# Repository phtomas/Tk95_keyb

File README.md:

Gerbers files to produce TK95 keyboard boards to substitute membranes. you can use original acetate and upper membrane to make contact for the keys, since at least key contact points are working. Or you can coat that points with some conduct ink or even stick some conduct material in that or use MX switches for a complete mechanical keyboard.

Based on Don Superfo schematics. original at: https://www.pcbway.com/project/shareproject/ZX_Spectrum_Keyboard_V2_14d9c665.html

Special thanks to Alexandre Simonka who has sponsered this project and Marlos Vasconcelos for moral support. Many thanks my friends.

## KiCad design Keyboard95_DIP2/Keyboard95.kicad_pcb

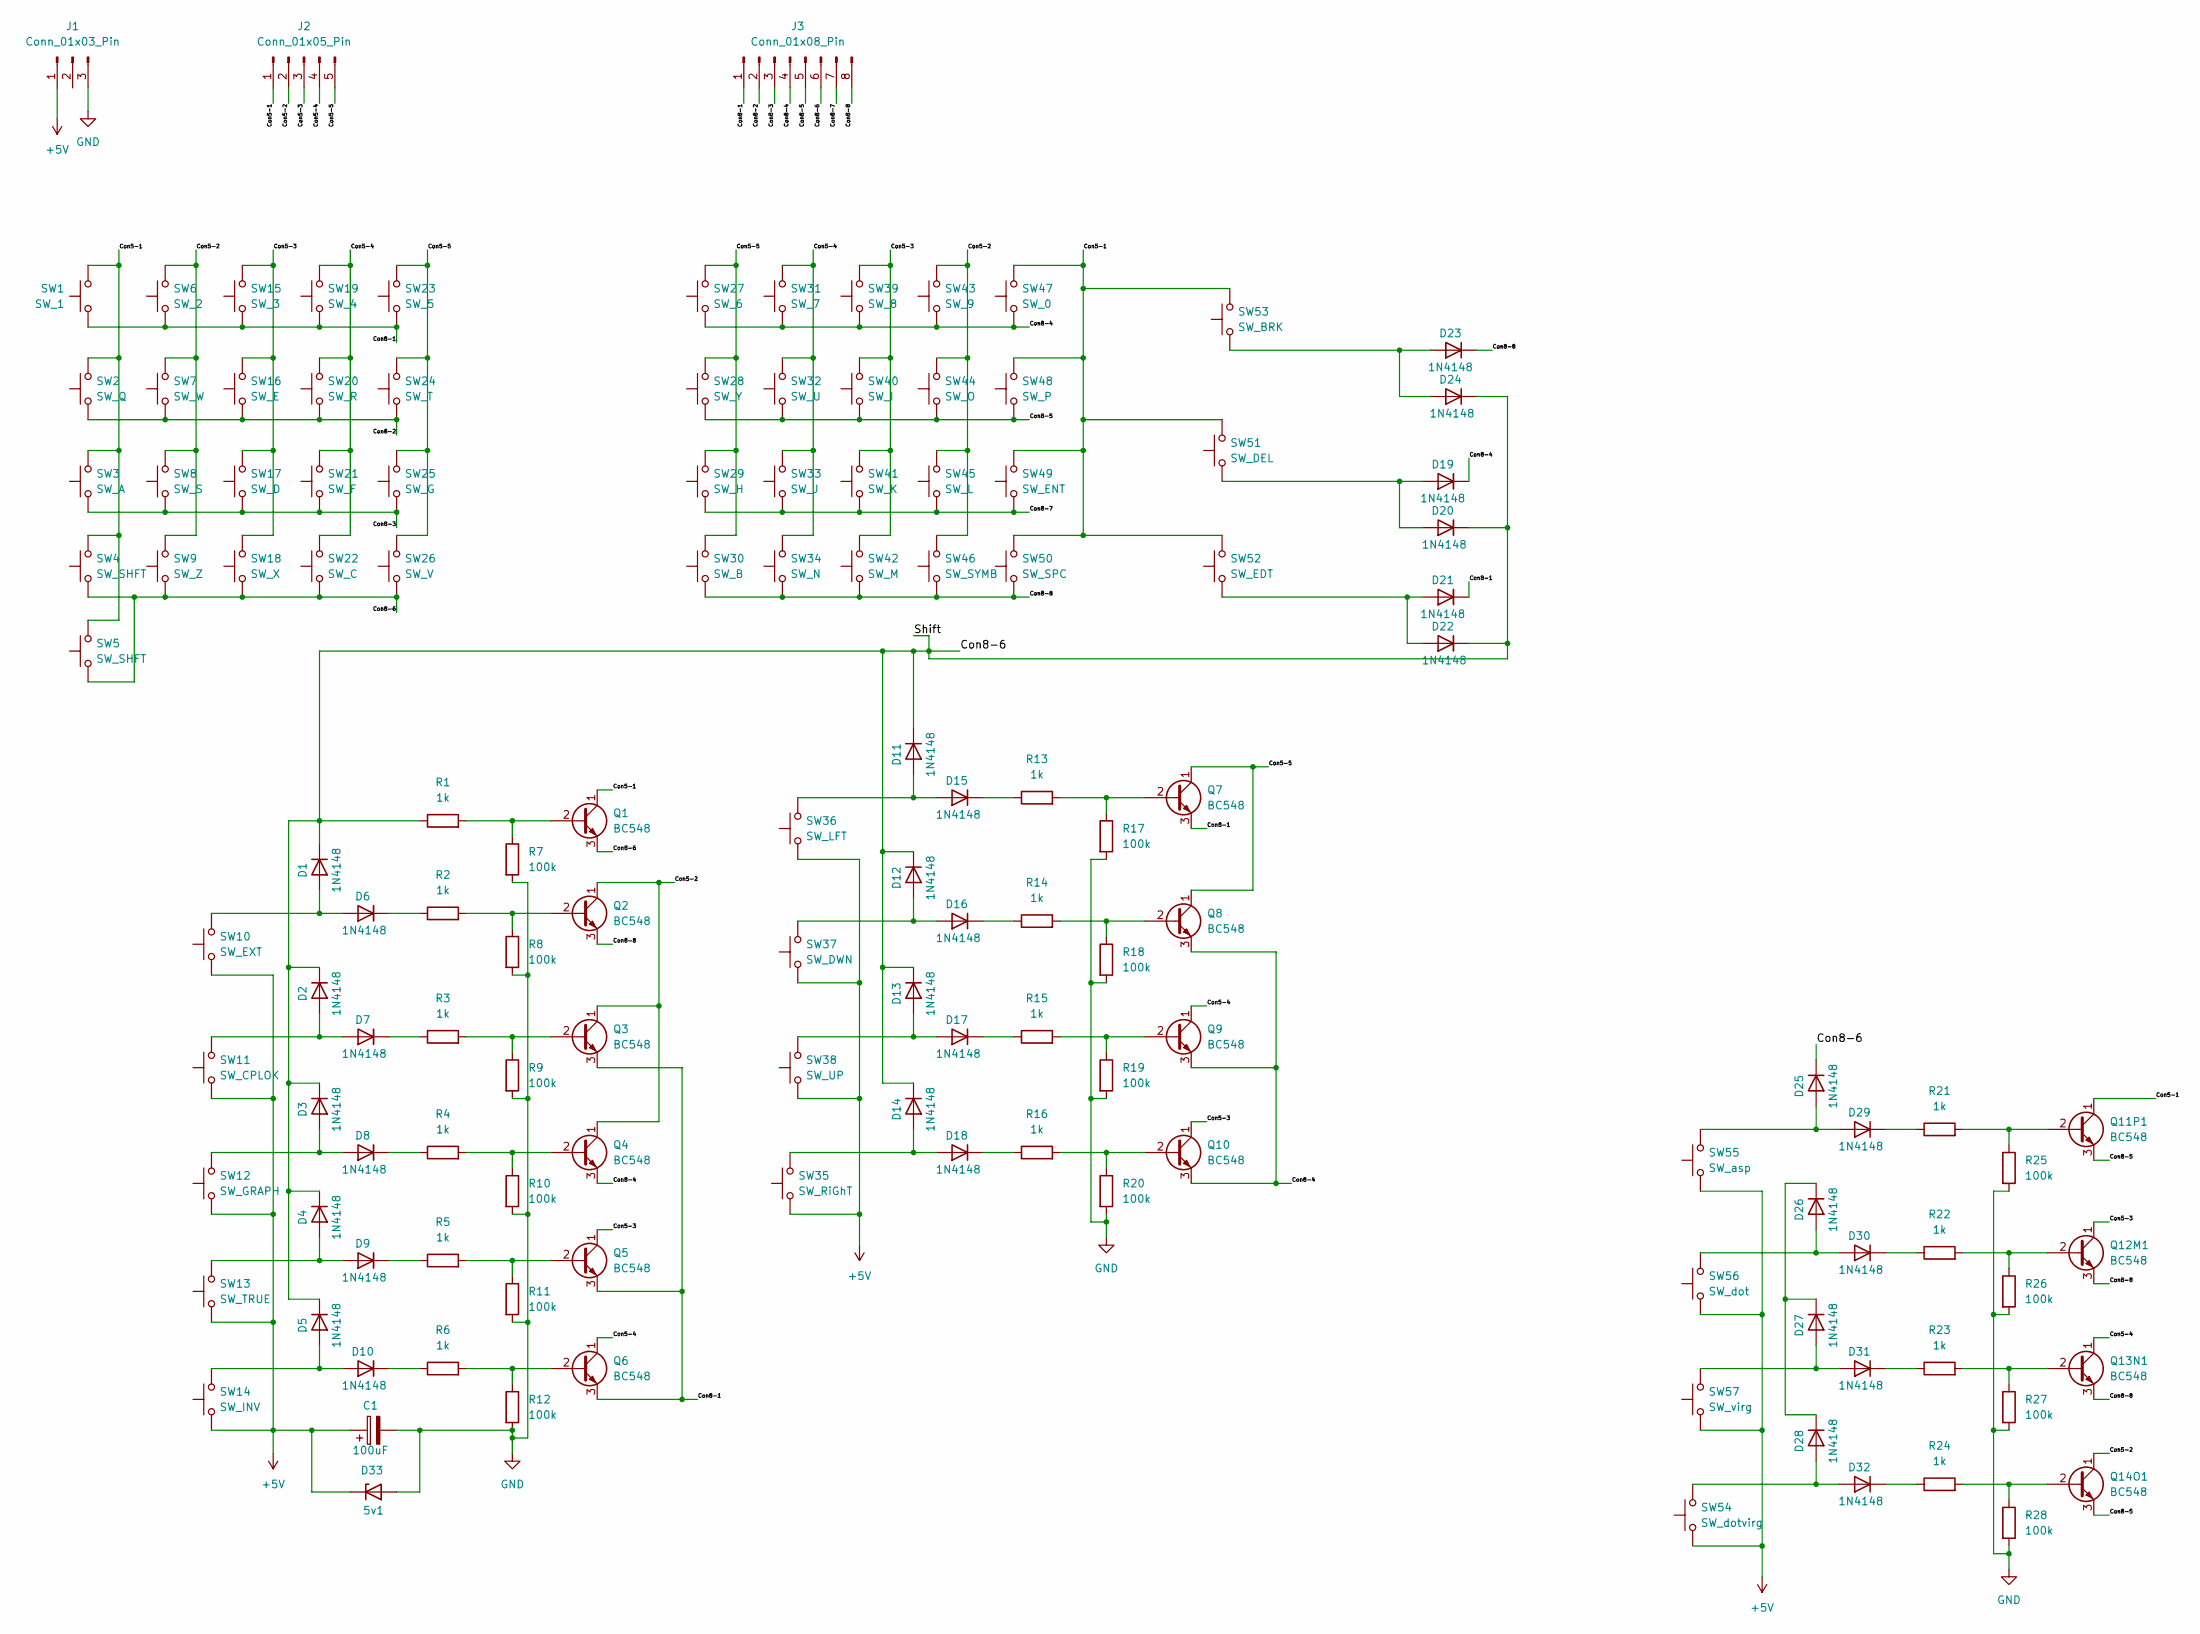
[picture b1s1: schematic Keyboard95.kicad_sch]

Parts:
C1: 100uF; CP_Radial_D5.0mm_P2.50mm
D1, D2, D3, D4, D5, D6, D7, D8, D9, D10, D11, D12, D13, D14, D15, D16, D17, D18, D19, D20, D21, D22, D23, D24, D25, D26, D27, D28, D29, D30, D31, D32: 1N4148; D_DO-35_SOD27_P7.62mm_Horizontal
D33: 5v1; D_A-405_P7.62mm_Horizontal
J1: Conn_01x03_Pin; PinHeader_1x03_P2.54mm_Vertical
J2: Conn_01x05_Pin; PinHeader_1x05_P2.54mm_Vertical
J3: Conn_01x08_Pin; PinHeader_1x08_P2.54mm_Vertical
Q1, Q2, Q3, Q4, Q5, Q6, Q7, Q8, Q9, Q10, Q11P1, Q12M1, Q13N1, Q14O1: BC548; TO-92_Inline
R1, R2, R3, R4, R5, R6, R13, R14, R15, R16, R21, R22, R23, R24: 1k; R_Box_L8.4mm_W2.5mm_P5.08mm
R7, R8, R9, R10, R11, R12, R17, R18, R19, R20, R25, R26, R27, R28: 100k; R_Box_L8.4mm_W2.5mm_P5.08mm
SW1: SW_1; SW_SMD_key
SW2: SW_Q; SW_SMD_key
SW3: SW_A; SW_SMD_key
SW4, SW5: SW_SHFT; SW_SMD_key
SW6: SW_2; SW_SMD_key
SW7: SW_W; SW_SMD_key
SW8: SW_S; SW_SMD_key
SW9: SW_Z; SW_SMD_key
SW10: SW_EXT; SW_SMD_key
SW11: SW_CPLOK; SW_SMD_key
SW12: SW_GRAPH; SW_SMD_key
SW13: SW_TRUE; SW_SMD_key
SW14: SW_INV; SW_SMD_key
SW15: SW_3; SW_SMD_key
SW16: SW_E; SW_SMD_key
SW17: SW_D; SW_SMD_key
SW18: SW_X; SW_SMD_key
SW19: SW_4; SW_SMD_key
SW20: SW_R; SW_SMD_key
SW21: SW_F; SW_SMD_key
SW22: SW_C; SW_SMD_key
SW23: SW_5; SW_SMD_key
SW24: SW_T; SW_SMD_key
SW25: SW_G; SW_SMD_key
SW26: SW_V; SW_SMD_key
SW27: SW_6; SW_SMD_key
SW28: SW_Y; SW_SMD_key
SW29: SW_H; SW_SMD_key
SW30: SW_B; SW_SMD_key
SW31: SW_7; SW_SMD_key
SW32: SW_U; SW_SMD_key
SW33: SW_J; SW_SMD_key
SW34: SW_N; SW_SMD_key
SW35: SW_RiGhT; SW_SMD_key
SW36: SW_LFT; SW_SMD_key
SW37: SW_DWN; SW_SMD_key
SW38: SW_UP; SW_SMD_key
SW39: SW_8; SW_SMD_key
SW40: SW_I; SW_SMD_key
SW41: SW_K; SW_SMD_key
SW42: SW_M; SW_SMD_key
SW43: SW_9; SW_SMD_key
SW44: SW_O; SW_SMD_key
SW45: SW_L; SW_SMD_key
SW46: SW_SYMB; SW_SMD_key
SW47: SW_0; SW_SMD_key
SW48: SW_P; SW_SMD_key
SW49: SW_ENT; SW_SMD_key
SW50: SW_SPC; SW_SMD_key
SW51: SW_DEL; SW_SMD_key
SW52: SW_EDT; SW_SMD_key
SW53: SW_BRK; SW_SMD_key
SW54: SW_dotvirg; SW_SMD_key
SW55: SW_asp; SW_SMD_key
SW56: SW_dot; SW_SMD_key
SW57: SW_virg; SW_SMD_key

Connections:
+5V: C1.1, D33.1 (K), J1.1, SW10.1, SW11.1, SW12.1, SW13.1, SW14.1, SW35.1, SW36.1, SW37.1, SW38.1, SW54.1, SW55.1, SW56.1, SW57.1
/Con5-1: J2.1, Q1.1 (C), Q11P1.1 (C), SW1.2, SW2.2, SW3.2, SW4.2, SW5.2, SW47.2, SW48.2, SW49.2, SW50.2, SW51.2, SW52.2, SW53.2
/Con5-2: J2.2, Q2.1 (C), Q3.1 (C), Q4.1 (C), Q14O1.1 (C), SW6.2, SW7.2, SW8.2, SW9.2, SW43.2, SW44.2, SW45.2, SW46.2
/Con5-3: J2.3, Q5.1 (C), Q10.1 (C), Q12M1.1 (C), SW15.2, SW16.2, SW17.2, SW18.2, SW39.2, SW40.2, SW41.2, SW42.2
/Con5-4: J2.4, Q6.1 (C), Q9.1 (C), Q13N1.1 (C), SW19.2, SW20.2, SW21.2, SW22.2, SW31.2, SW32.2, SW33.2, SW34.2
/Con5-5: J2.5, Q7.1 (C), Q8.1 (C), SW23.2, SW24.2, SW25.2, SW26.2, SW27.2, SW28.2, SW29.2, SW30.2
/Con8-1: D21.1 (K), J3.1, Q3.3 (E), Q5.3 (E), Q6.3 (E), Q7.3 (E), SW1.1, SW6.1, SW15.1, SW19.1, SW23.1
/Con8-2: J3.2, SW2.1, SW7.1, SW16.1, SW20.1, SW24.1
/Con8-3: J3.3, SW3.1, SW8.1, SW17.1, SW21.1, SW25.1
/Con8-4: D19.1 (K), J3.4, Q4.3 (E), Q8.3 (E), Q9.3 (E), Q10.3 (E), SW27.1, SW31.1, SW39.1, SW43.1, SW47.1
/Con8-5: J3.5, Q11P1.3 (E), Q14O1.3 (E), SW28.1, SW32.1, SW40.1, SW44.1, SW48.1
/Con8-6: D1.1 (K), D2.1 (K), D3.1 (K), D4.1 (K), D5.1 (K), D11.1 (K), D12.1 (K), D13.1 (K), D14.1 (K), D20.1 (K), D22.1 (K), D24.1 (K), D25.1 (K), J3.6, Q1.3 (E), R1.1, SW4.1, SW5.1, SW9.1, SW18.1, SW22.1, SW26.1
/Con8-7: J3.7, SW29.1, SW33.1, SW41.1, SW45.1, SW49.1
/Con8-8: D23.1 (K), J3.8, Q2.3 (E), Q12M1.3 (E), Q13N1.3 (E), SW30.1, SW34.1, SW42.1, SW46.1, SW50.1
GND: C1.2, D33.2 (A), J1.3, R7.2, R8.2, R9.2, R10.2, R11.2, R12.2, R17.2, R18.2, R19.2, R20.2, R25.2, R26.2, R27.2, R28.2
unnamed: D1.2 (A), D6.2 (A), SW10.2
unnamed: D2.2 (A), D7.2 (A), SW11.2
unnamed: D3.2 (A), D8.2 (A), SW12.2
unnamed: D4.2 (A), D9.2 (A), SW13.2
unnamed: D6.1 (K), R2.1
unnamed: D7.1 (K), R3.1
unnamed: D8.1 (K), R4.1
unnamed: D9.1 (K), R5.1
unnamed: D5.2 (A), D10.2 (A), SW14.2
unnamed: D10.1 (K), R6.1
unnamed: D11.2 (A), D15.2 (A), SW36.2
unnamed: D12.2 (A), D16.2 (A), SW37.2
unnamed: D13.2 (A), D17.2 (A), SW38.2
unnamed: D14.2 (A), D18.2 (A), SW35.2
unnamed: D15.1 (K), R13.1
unnamed: D16.1 (K), R14.1
unnamed: D17.1 (K), R15.1
unnamed: D18.1 (K), R16.1
unnamed: D19.2 (A), D20.2 (A), SW51.1
unnamed: D21.2 (A), D22.2 (A), SW52.1
unnamed: D23.2 (A), D24.2 (A), SW53.1
unnamed: D25.2 (A), D29.2 (A), SW55.2
unnamed: D26.2 (A), D30.2 (A), SW56.2
unnamed: D26.1 (K), D27.1 (K), D28.1 (K)
unnamed: D27.2 (A), D31.2 (A), SW57.2
unnamed: D28.2 (A), D32.2 (A), SW54.2
unnamed: D29.1 (K), R21.1
unnamed: D30.1 (K), R22.1
unnamed: D31.1 (K), R23.1
unnamed: D32.1 (K), R24.1
unnamed: Q1.2 (B), R1.2, R7.1
unnamed: Q2.2 (B), R2.2, R8.1
unnamed: Q3.2 (B), R3.2, R9.1
unnamed: Q4.2 (B), R4.2, R10.1
unnamed: Q5.2 (B), R5.2, R11.1
unnamed: Q6.2 (B), R6.2, R12.1
unnamed: Q7.2 (B), R13.2, R17.1
unnamed: Q8.2 (B), R14.2, R18.1
unnamed: Q9.2 (B), R15.2, R19.1
unnamed: Q10.2 (B), R16.2, R20.1
unnamed: Q11P1.2 (B), R21.2, R25.1
unnamed: Q12M1.2 (B), R22.2, R26.1
unnamed: Q13N1.2 (B), R23.2, R27.1
unnamed: Q14O1.2 (B), R24.2, R28.1

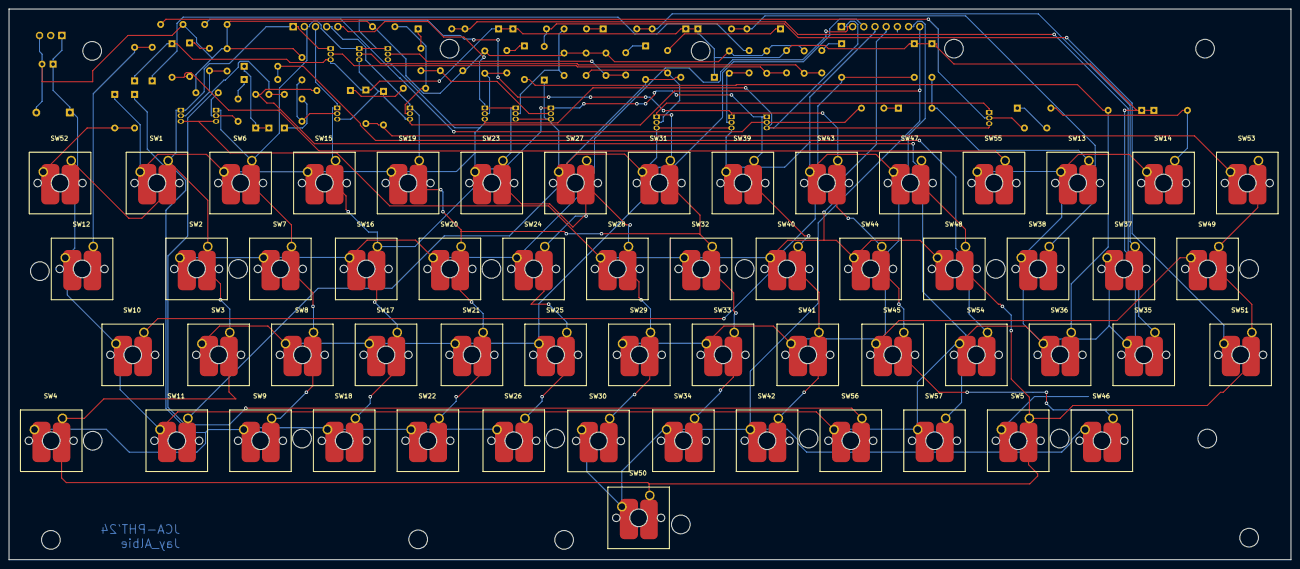
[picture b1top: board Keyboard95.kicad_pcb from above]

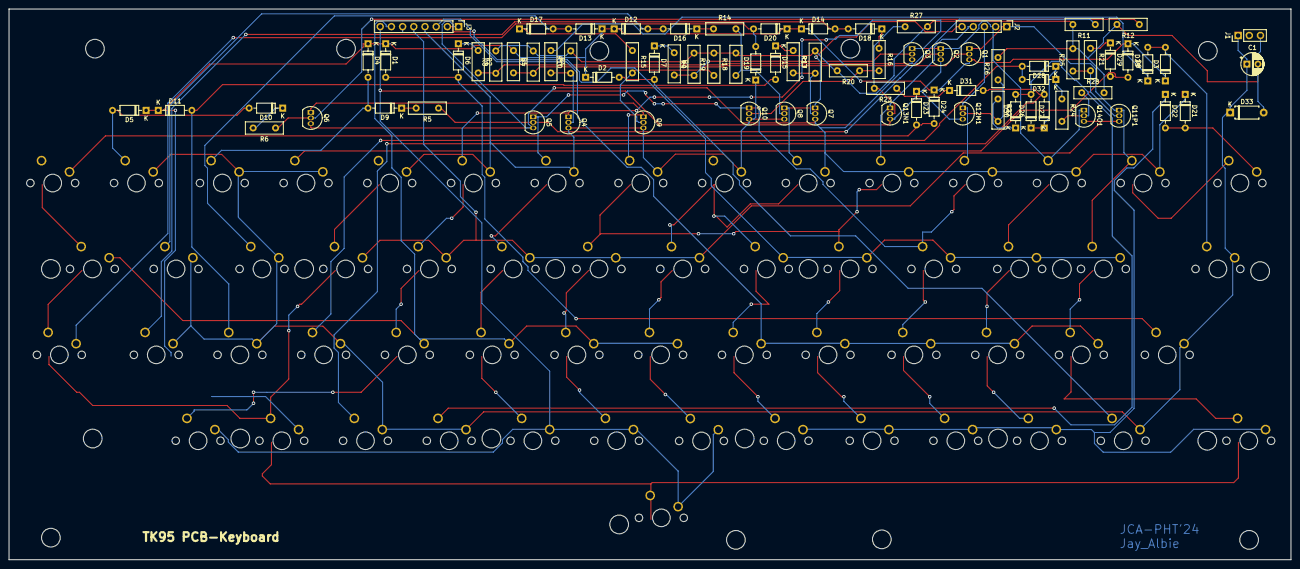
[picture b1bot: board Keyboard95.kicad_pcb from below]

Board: 2 copper layers, 291.0 x 125.0 mm, 136 parts (79 on the bottom side), 59 nets.

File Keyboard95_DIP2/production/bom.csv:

Designator,Footprint,Quantity,Value,LCSC Part #
C1,CP_Radial_D5.0mm_P2.50mm,1,100uF,
"D1, D10, D11, D12, D13, D14, D15, D16, D17, D18, D19, D2, D20, D21, D22, D23, D24, D25, D26, D27, D28, D29, D3, D30, D31, D32, D4, D5, D6, D7, D8, D9",D_DO-35_SOD27_P7.62mm_Horizontal,32,1N4148,
D33,D_A-405_P7.62mm_Horizontal,1,5v1,
J1,PinHeader_1x03_P2.54mm_Vertical,1,Conn_01x03_Pin,
J2,PinHeader_1x05_P2.54mm_Vertical,1,Conn_01x05_Pin,
J3,PinHeader_1x08_P2.54mm_Vertical,1,Conn_01x08_Pin,
"Q1, Q10, Q11P1, Q12M1, Q13N1, Q14O1, Q2, Q3, Q4, Q5, Q6, Q7, Q8, Q9",TO-92_Inline,14,BC548,
"R1, R13, R14, R15, R16, R2, R21, R22, R23, R24, R3, R4, R5, R6",R_Box_L8.4mm_W2.5mm_P5.08mm,14,1k,
"R10, R11, R12, R17, R18, R19, R20, R25, R26, R27, R28, R7, R8, R9",R_Box_L8.4mm_W2.5mm_P5.08mm,14,100k,
SW1,SW_SMD_key,1,SW_1,
SW10,SW_SMD_key,1,SW_EXT,
SW11,SW_SMD_key,1,SW_CPLOK,
SW12,SW_SMD_key,1,SW_GRAPH,
SW13,SW_SMD_key,1,SW_TRUE,
SW14,SW_SMD_key,1,SW_INV,
SW15,SW_SMD_key,1,SW_3,
SW16,SW_SMD_key,1,SW_E,
SW17,SW_SMD_key,1,SW_D,
SW18,SW_SMD_key,1,SW_X,
SW19,SW_SMD_key,1,SW_4,
SW2,SW_SMD_key,1,SW_Q,
SW20,SW_SMD_key,1,SW_R,
SW21,SW_SMD_key,1,SW_F,
SW22,SW_SMD_key,1,SW_C,
SW23,SW_SMD_key,1,SW_5,
SW24,SW_SMD_key,1,SW_T,
SW25,SW_SMD_key,1,SW_G,
SW26,SW_SMD_key,1,SW_V,
SW27,SW_SMD_key,1,SW_6,
SW28,SW_SMD_key,1,SW_Y,
SW29,SW_SMD_key,1,SW_H,
SW3,SW_SMD_key,1,SW_A,
SW30,SW_SMD_key,1,SW_B,
SW31,SW_SMD_key,1,SW_7,
SW32,SW_SMD_key,1,SW_U,
SW33,SW_SMD_key,1,SW_J,
SW34,SW_SMD_key,1,SW_N,
SW35,SW_SMD_key,1,SW_RiGhT,
SW36,SW_SMD_key,1,SW_LFT,
SW37,SW_SMD_key,1,SW_DWN,
SW38,SW_SMD_key,1,SW_UP,
SW39,SW_SMD_key,1,SW_8,
"SW4, SW5",SW_SMD_key,2,SW_SHFT,
SW40,SW_SMD_key,1,SW_I,
SW41,SW_SMD_key,1,SW_K,
SW42,SW_SMD_key,1,SW_M,
SW43,SW_SMD_key,1,SW_9,
SW44,SW_SMD_key,1,SW_O,
SW45,SW_SMD_key,1,SW_L,
SW46,SW_SMD_key,1,SW_SYMB,
SW47,SW_SMD_key,1,SW_0,
SW48,SW_SMD_key,1,SW_P,
SW49,SW_SMD_key,1,SW_ENT,
SW50,SW_SMD_key,1,SW_SPC,
SW51,SW_SMD_key,1,SW_DEL,
SW52,SW_SMD_key,1,SW_EDT,
SW53,SW_SMD_key,1,SW_BRK,
SW54,SW_SMD_key,1,SW_dotvirg,
SW55,SW_SMD_key,1,SW_asp,
SW56,SW_SMD_key,1,SW_dot,
SW57,SW_SMD_key,1,SW_virg,
SW6,SW_SMD_key,1,SW_2,
SW7,SW_SMD_key,1,SW_W,
SW8,SW_SMD_key,1,SW_S,
SW9,SW_SMD_key,1,SW_Z,

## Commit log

2026-01-08 Add project details and acknowledgments to README
    Added information about TK95 keyboard boards and acknowledgments.
2026-01-08 Rename WhatsApp Image 2026-01-07 at 16.08.14.jpeg to keyb92_mx.jpeg
2026-01-08 Rename keyb92_mx.jpeg to keyb95_mx.jpeg
2026-01-09 Update README with project references and acknowledgments
